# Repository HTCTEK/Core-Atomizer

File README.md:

## Core Module
    Core Modules 是给那些想尽可能少花费又可以快速实现或者验证某些功能的用户。
    Core Modules just for users who want to make or verify somthing as soon as possible whith a low cost.

## 怎么用 / How to Use
1. 买一个 / Buy One: [Click](https://taobao.com)
2. 看说明 / Read Me：[Click](https://pinno.cc)
3. 动手做 / Just Do it

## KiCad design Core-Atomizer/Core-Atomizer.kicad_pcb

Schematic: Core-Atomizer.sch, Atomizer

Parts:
C1, C2, C3: 330pF; C_0402_1005Metric; PartNumber 0402B331K500NT
C4: 22uF; C_0805_2012Metric; PartNumber CL21A226MAQNNNE
J1: PH-4AW; JST_PH_S4B-PH-K_1x04_P2.00mm_Horizontal; PartNumber PH-4AW
J2: PH-2AW环保; JST_PH_S2B-PH-K_1x02_P2.00mm_Horizontal; PartNumber PH-2AW环保
L1: IND_3Pins_22uH_720uH_6x8mm; Inductor_3Pins_6x8mm; PartNumber None
Q1, Q2: CJ2102; SOT-323_SC-70; PartNumber CJ2102
R1, R4, R6: 10k; R_0402_1005Metric; PartNumber 0402WGF1002TCE
R2, R3, R5: 1k; R_0402_1005Metric; PartNumber 0402WGF1001TCE
U1: NL17SZ14DFT2G; SOT-353_SC-70-5; PartNumber NL17SZ14DFT2G

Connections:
/ENABLE: J1.3, R5.2
/PWM: J1.4, R3.2
/VCC: C3.1, C4.1, J1.2, J2.2, L1.1, U1.5 (VCC); also elsewhere on the board
Earth: C4.2, J1.1, Q2.2 (S), R6.2
GND: C2.2, Q1.2 (S), Q2.3 (D), R4.2, U1.3 (GND)
unnamed: C2.1, R1.1, U1.2 (INA)
unnamed: C3.2, L1.2, Q1.3 (D)
unnamed 7: J2.1, L1.3; also elsewhere on the board
unnamed: Q1.1 (G), R2.2, R3.1, R4.1
unnamed: Q2.1 (G), R5.1, R6.1
unnamed: R1.2, R2.1, U1.4 (OUT_~Y)

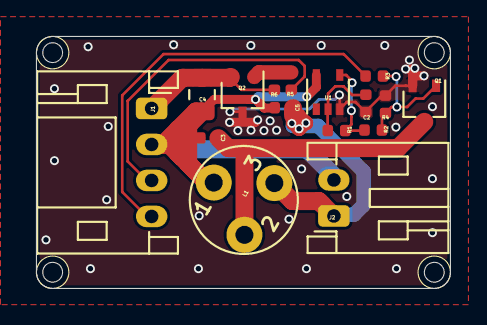
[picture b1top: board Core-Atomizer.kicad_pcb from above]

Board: 2 copper layers, 23.0 x 14.0 mm, 16 parts (0 on the bottom side), 11 nets.

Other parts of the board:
C5: 2.2nF; C_0402_1005Metric

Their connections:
/VCC: C5.1; also elsewhere on the board
unnamed 7: C5.2; also elsewhere on the board

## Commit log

2020-02-29 v0.1 打样
2020-02-29 订正inductor封装，增加丝印
2020-02-29 add LICENSE.
2020-02-29 增加readme
2020-02-29 修改readme
2020-03-05 更改升压电感的错误引脚号，3->2,2->3,并变更PCB
2020-03-05 debug震荡电容为2.2nF,震荡频率实测40~50kHz
